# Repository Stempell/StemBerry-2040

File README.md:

# StemBerry-2040
A RP2040 devboard! Im doing it for Hack Club's Macondo program. It features two buttons for reset and bootsel and two onboard led's (one for power and one is hooked up to pin15), and also a cool evangelion-themed silkscreen art!
It plugs in to breadboards an female headers just like a standard pi pico.
I made this project to learn about making microcontrollers and more advanced pcb's and to have some microcontrollers for personal use. This project taught me a lot and it was also my first time working with restricted space on the board, so every trace and component placement had to be well thought.

The button on the left enters into BOOTSEL mode. The one on the right resets the board.
To upload code press the BOOTSEL button while booting up the board. It will then appear as a USB device on your pc, so you can drop the code in.

## Schematic

## Pcb

The dimensions are 21 x 51mm

## Full Bulid!

Here's the finished thing! :

## Bill of materials

| Component | Qty / board | Order qty | Ext. price | JLCPCB part |
|---|---|---|---|---|
| RP2040 | 1 | 5 | $4.94 | [C2040](https://jlcpcb.com/partdetail/C2040) |
| W25Q16JVUXIQ (flash) | 1 | 5 | $8.02 | [C2843335](https://jlcpcb.com/partdetail/C2843335) |
| XC6206P332MR-G (3.3V LDO) | 1 | 5 | $0.66 | [C5446](https://jlcpcb.com/partdetail/C5446) |
| 12MHz crystal | 1 | 5 | $0.47 | [C9002](https://jlcpcb.com/partdetail/C9002) |
| USB_C_Receptacle_USB2.0_14P | 1 | 5 | $0.92 | [C165948](https://jlcpcb.com/partdetail/C165948) |
| SW_Push | 2 | 10 | $0.55 | [C720477](https://jlcpcb.com/partdetail/C720477) |
| 100nF | 12 | 60 | $0.32 | [C1525](https://jlcpcb.com/partdetail/C1525) |
| 1uF | 2 | 10 | $0.16 | [C52923](https://jlcpcb.com/partdetail/C52923) |
| 10uF | 2 | 10 | $0.39 | [C19702](https://jlcpcb.com/partdetail/C19702) |
| 33pF | 2 | 10 | $0.07 | [C1562](https://jlcpcb.com/partdetail/C1562) |
| 5.1K | 2 | 10 | $0.06 | [C25905](https://jlcpcb.com/partdetail/C25905) |
| 27 | 2 | 20 | $0.03 | [C25156](https://jlcpcb.com/partdetail/C25156) |
| 1K | 2 | 10 | $0.07 | [C11702](https://jlcpcb.com/partdetail/C11702) |
| 10K | 1 | 5 | $0.04 | [C25744](https://jlcpcb.com/partdetail/C25744) |
| 330 | 1 | 5 | $0.04 | [C25104](https://jlcpcb.com/partdetail/C25104) |
| 470 | 1 | 5 | $0.03 | [C25117](https://jlcpcb.com/partdetail/C25117) |
| 100K | 1 | 5 | $0.04 | [C25741](https://jlcpcb.com/partdetail/C25741) |
| LED (0603) | 1 | 5 | $0.04 | [C2286](https://jlcpcb.com/partdetail/C2286) |
| LED (0805) | 1 | 5 | $0.08 | [C2297](https://jlcpcb.com/partdetail/C2297) |
| **Total** | | | **$16.93** | |

Additional charges and assembly costs rung me up $26.13
You will also need to hand solder two 1x20 male to male pin headers like these ones for like $3.17:

https://pl.aliexpress.com/item/1005007486600604.html?spm=a2g0o.detail.pcDetailTopMoreOtherSeller.1.3aacPweuPweunK&gps-id=pcDetailTopMoreOtherSeller&scm=1007.40050.354490.0&scm_id=1007.40050.354490.0&scm-url=1007.40050.354490.0&pvid=687313aa-89cb-461f-b6b6-9fdf85656003&_t=gps-id%3ApcDetailTopMoreOtherSeller%2Cscm-url%3A1007.40050.354490.0%2Cpvid%3A687313aa-89cb-461f-b6b6-9fdf85656003%2Ctpp_buckets%3A668%232846%238111%231996&pdp_ext_f=%7B%22order%22%3A%221255%22%2C%22eval%22%3A%221%22%2C%22sceneId%22%3A%2230050%22%2C%22fromPage%22%3A%22recommend%22%7D&pdp_npi=6%40dis%21PLN%214.29%214.29%21%21%211.12%211.12%21%400b88abba17864469134574151e101b%2112000040991067942%21rec%21PL%216850984236%21XZ%211%210%21n_tag%3A-29919%3Bd%3A9d0c4368%3Bm03_new_user%3A-29895&utparam-url=scene%3ApcDetailTopMoreOtherSeller%7Cquery_from%3A%7Cx_object_id%3A1005007486600604%7C_p_origin_prod%3A

Total cost: $44.43

If you wish to learn how to make a devboard like this one yourself, or any other devboard similar to this one check out the guide i used:

https://macondo.hackclub.com/docs/build-a-devboard

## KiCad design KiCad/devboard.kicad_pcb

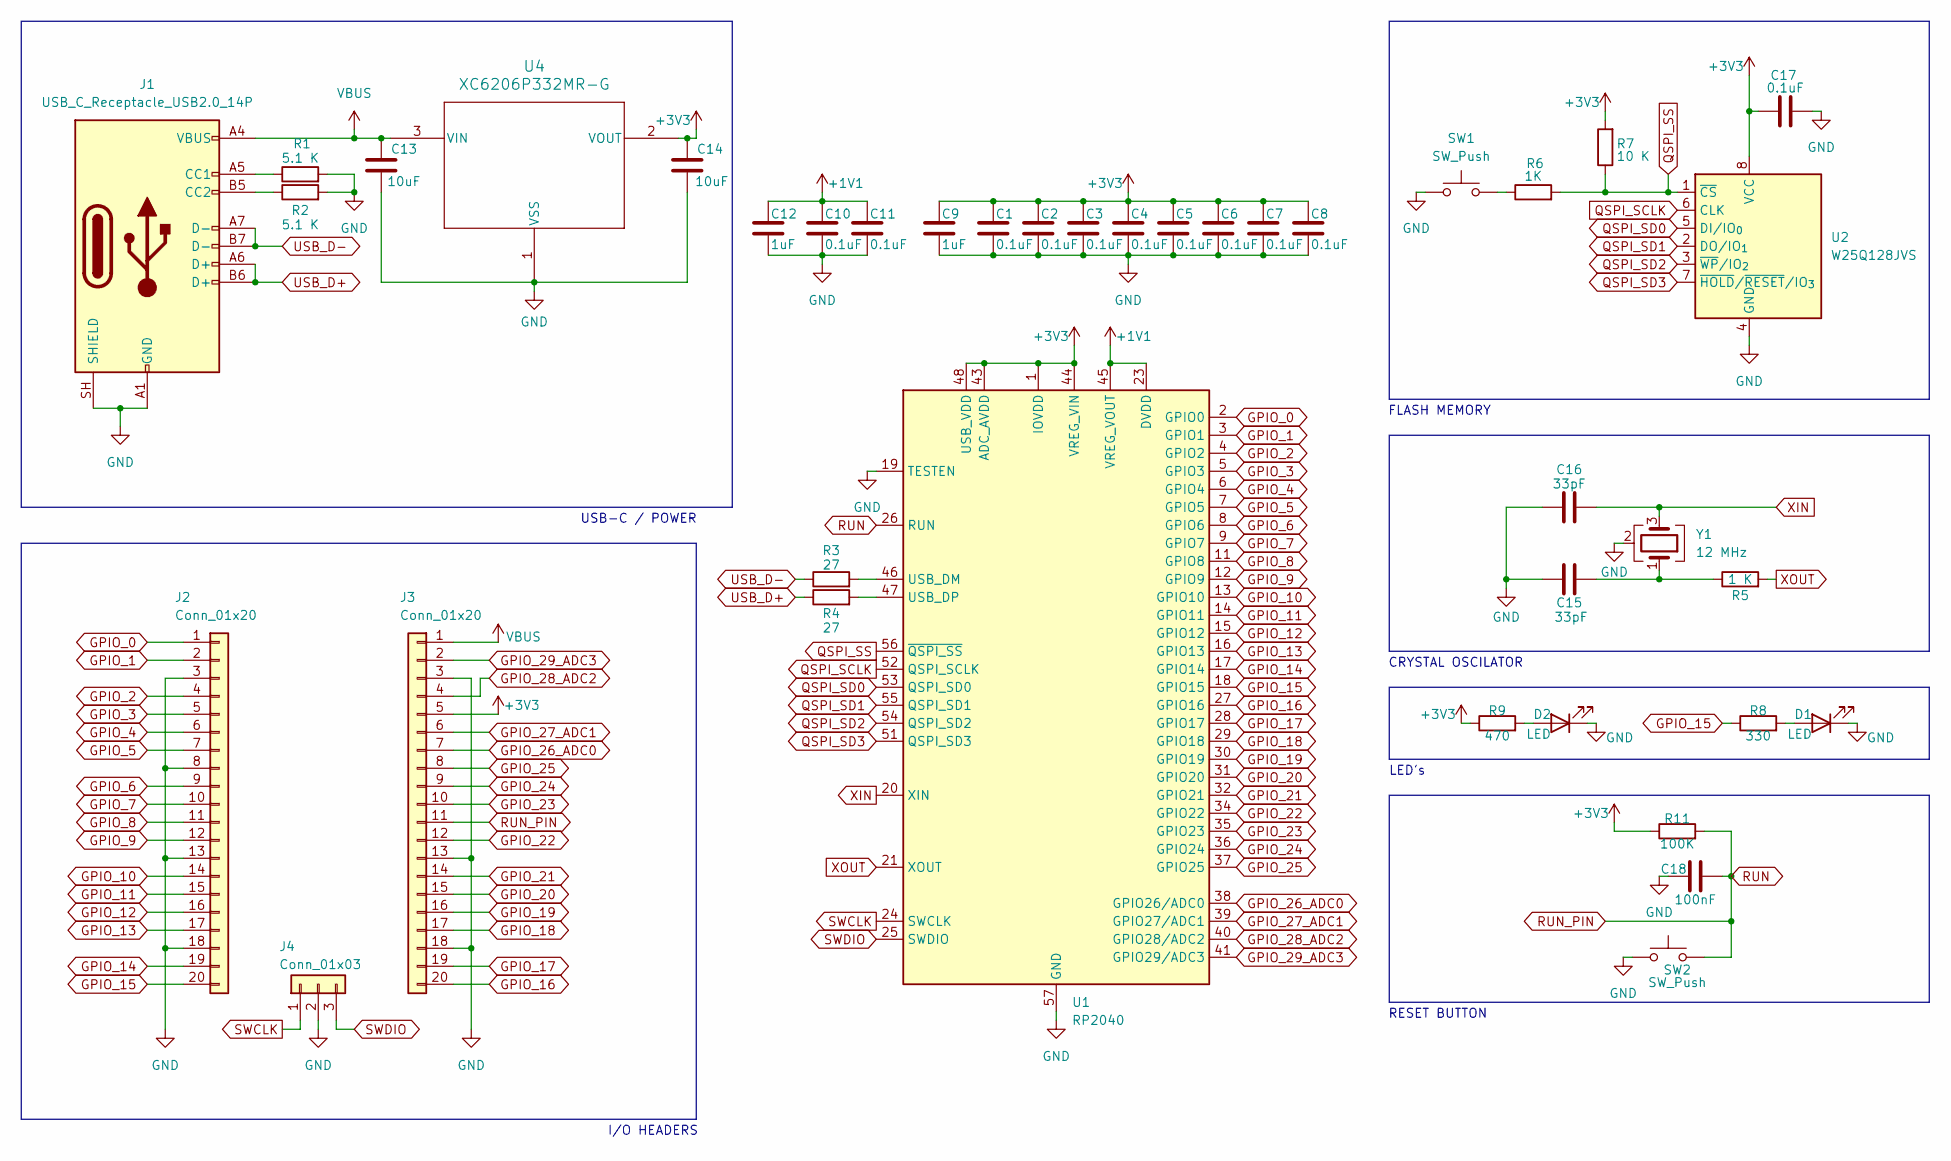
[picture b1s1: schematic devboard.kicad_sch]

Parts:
C1, C2, C3, C4, C5, C6, C7, C8, C10, C11, C17: 0.1uF; C_0402_1005Metric
C9, C12: 1uF; C_0402_1005Metric
C13, C14: 10uF; C_0603_1608Metric
C15, C16: 33pF; C_0402_1005Metric
C18: 100nF; C_0402_1005Metric
D1, D2: LED; LED_0603_1608Metric
J1: USB_C_Receptacle_USB2.0_14P; USB_C_Receptacle_HRO_TYPE-C-31-M-12
J2, J3: Conn_01x20; PinHeader_1x20_P2.54mm_Vertical
J4: Conn_01x03; PinHeader_1x03_P2.54mm_Vertical
R1, R2: 5.1 K; R_0402_1005Metric
R3, R4: 27; R_0402_1005Metric
R5: 1 K; R_0402_1005Metric
R6: 1K; R_0402_1005Metric
R7: 10 K; R_0402_1005Metric
R8: 330; R_0402_1005Metric
R9: 470; R_0402_1005Metric
R11: 100K; R_0402_1005Metric
SW1, SW2: SW_Push; SW_Push_SPST_NO_Alps_SKRK
U1: RP2040; QFN-56-1EP_7x7mm_P0.4mm_EP3.2x3.2mm
U2: W25Q128JVS; Winbond_USON-8-1EP_3x2mm_P0.5mm_EP0.2x1.6mm
U4: XC6206P332MR-G; SOT-23-3
Y1: 12 MHz; Crystal_SMD_3225-4Pin_3.2x2.5mm

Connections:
+1V1: C10.1, C11.1, C12.1, U1.23 (DVDD), U1.45 (VREG_VOUT), U1.50 (DVDD)
+3V3: C1.1, C2.1, C3.1, C4.1, C5.1, C6.1, C7.1, C8.1, C9.1, C14.1, C17.1, J3.5, R7.2, R9.1, R11.1, U1.1 (IOVDD), U1.10 (IOVDD), U1.22 (IOVDD), U1.33 (IOVDD), U1.42 (IOVDD), U1.43 (ADC_AVDD), U1.44 (VREG_VIN), U1.48 (USB_VDD), U1.49 (IOVDD), U2.8 (VCC), U4.2 (VOUT); also elsewhere on the board
GND: C1.2, C2.2, C3.2, C4.2, C5.2, C6.2, C7.2, C8.2, C9.2, C10.2, C11.2, C12.2, C13.2, C14.2, C15.1, C16.1, C17.2, C18.1, D1.1 (K), D2.1 (K), J1.A1 (GND), J1.A12 (GND), J1.B1 (GND), J1.B12 (GND), J1.SH (SHIELD), J2.3, J2.8, J2.13, J2.18, J3.3, J3.13, J3.18, J4.2, R1.2, R2.2, SW1.1, SW2.1, U1.19 (TESTEN), U1.57 (GND), U2.4 (GND), U4.1 (VSS), Y1.2 (G), Y1.4 (G); also elsewhere on the board
GPIO_0: J2.1, U1.2 (GPIO0)
GPIO_1: J2.2, U1.3 (GPIO1)
GPIO_2: J2.4, U1.4 (GPIO2)
GPIO_3: J2.5, U1.5 (GPIO3)
GPIO_4: J2.6, U1.6 (GPIO4)
GPIO_5: J2.7, U1.7 (GPIO5)
GPIO_6: J2.9, U1.8 (GPIO6)
GPIO_7: J2.10, U1.9 (GPIO7)
GPIO_8: J2.11, U1.11 (GPIO8)
GPIO_9: J2.12, U1.12 (GPIO9)
GPIO_10: J2.14, U1.13 (GPIO10)
GPIO_11: J2.15, U1.14 (GPIO11)
GPIO_12: J2.16, U1.15 (GPIO12)
GPIO_13: J2.17, U1.16 (GPIO13)
GPIO_14: J2.19, U1.17 (GPIO14)
GPIO_15: J2.20, R8.1, U1.18 (GPIO15)
GPIO_16: J3.20, U1.27 (GPIO16)
GPIO_17: J3.19, U1.28 (GPIO17)
GPIO_18: J3.17, U1.29 (GPIO18)
GPIO_19: J3.16, U1.30 (GPIO19)
GPIO_20: J3.15, U1.31 (GPIO20)
GPIO_21: J3.14, U1.32 (GPIO21)
GPIO_22: J3.12, U1.34 (GPIO22)
GPIO_23: J3.10, U1.35 (GPIO23)
GPIO_24: J3.9, U1.36 (GPIO24)
GPIO_25: J3.8, U1.37 (GPIO25)
GPIO_26_ADC0: J3.7, U1.38 (GPIO26/ADC0)
GPIO_27_ADC1: J3.6, U1.39 (GPIO27/ADC1)
GPIO_28_ADC2: J3.4, U1.40 (GPIO28/ADC2)
GPIO_29_ADC3: J3.2, U1.41 (GPIO29/ADC3)
unnamed: C15.2, R5.1, Y1.1
unnamed: D1.2 (A), R8.2
unnamed: D2.2 (A), R9.2
unnamed: J1.A5 (CC1), R1.1
unnamed: J1.B5 (CC2), R2.1
unnamed: R6.1, SW1.2
unnamed: R3.2, U1.46 (USB_DM)
unnamed: R4.2, U1.47 (USB_DP)
QSPI_SCLK: U1.52 (QSPI_SCLK), U2.6 (CLK)
QSPI_SD0: U1.53 (QSPI_SD0), U2.5 (DI/IO_{0})
QSPI_SD1: U1.55 (QSPI_SD1), U2.2 (DO/IO_{1})
QSPI_SD2: U1.54 (QSPI_SD2), U2.3 (~WP/IO_{2})
QSPI_SD3: U1.51 (QSPI_SD3), U2.7 (~HOLD/~RESET/IO_{3})
QSPI_SS: R6.2, R7.1, U1.56 (~QSPI_SS), U2.1 (~CS)
RUN: C18.2, J3.11, R11.2, SW2.2, U1.26 (RUN)
SWCLK: J4.1, U1.24 (SWCLK)
SWDIO: J4.3, U1.25 (SWDIO)
USB_D+: J1.A6 (D+), J1.B6 (D+), R4.1
USB_D-: J1.A7 (D-), J1.B7 (D-), R3.1
VBUS: C13.1, J1.A4 (VBUS), J1.A9 (VBUS), J1.B4 (VBUS), J1.B9 (VBUS), J3.1, U4.3 (VIN); also elsewhere on the board
XIN: C16.2, U1.20 (XIN), Y1.3
XOUT: R5.2, U1.21 (XOUT)

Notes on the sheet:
I/O HEADERS
USB-C / POWER
FLASH MEMORY
LED's
CRYSTAL OSCILATOR
RESET BUTTON

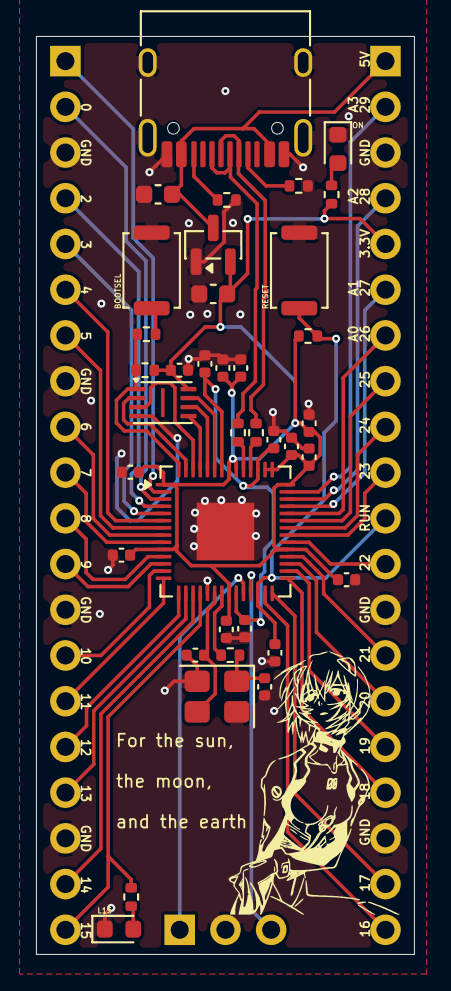
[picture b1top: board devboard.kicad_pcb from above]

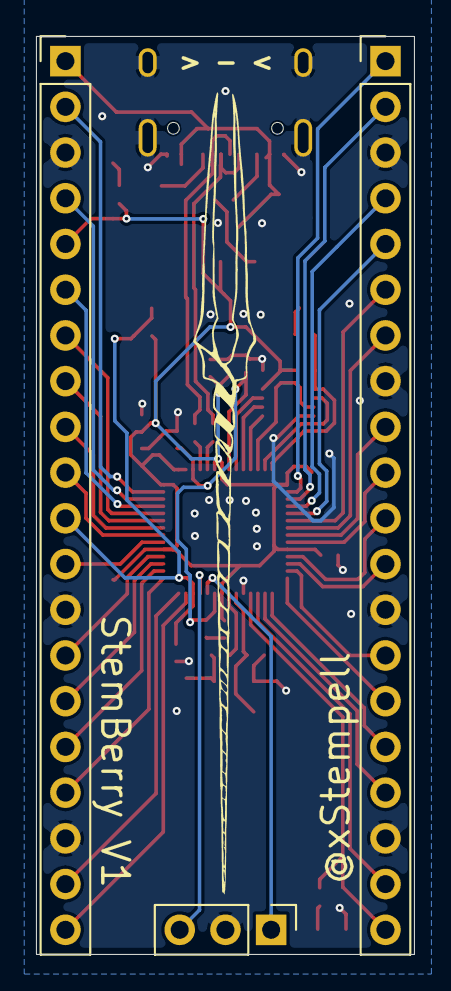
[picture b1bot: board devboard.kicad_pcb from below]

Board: 2 copper layers, 21.0 x 51.0 mm, 40 parts (3 on the bottom side), 55 nets.

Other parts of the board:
U3: MCP1700x-330xxTT; SOT-23

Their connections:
+3V3: U3.2 (VO); also elsewhere on the board
GND: U3.1 (GND); also elsewhere on the board
VBUS: U3.3 (VI); also elsewhere on the board

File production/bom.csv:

Designator,Footprint,Quantity,Value,LCSC Part #
"C1, C10, C11, C17, C2, C3, C4, C5, C6, C7, C8",0402,11,0.1uF,
"C12, C9",0402,2,1uF,
"C13, C14",0603,2,10uF,
"C15, C16",0402,2,33pF,
C18,0402,1,100nF,
"D1, D2",0603,2,LED,
J1,USB_C_Receptacle_HRO_TYPE-C-31-M-12,1,USB_C_Receptacle_USB2.0_14P,
"J2, J3",PinHeader_1x20_P2.54mm_Vertical,2,Conn_01x20,
J4,PinHeader_1x03_P2.54mm_Vertical,1,Conn_01x03,
"R1, R2",0402,2,5.1 K,
R11,0402,1,100K,
"R3, R4",0402,2,27,
R5,0402,1,1 K,
R6,0402,1,1K,
R7,0402,1,10 K,
R8,0402,1,330,
R9,0402,1,470,
"SW1, SW2",SW_Push_SPST_NO_Alps_SKRK,2,SW_Push,
U1,QFN-56-1EP_7x7mm_P0.4mm_EP3.2x3.2mm,1,RP2040,
U2,Winbond_USON-8-1EP_3x2mm_P0.5mm_EP0.2x1.6mm,1,W25Q128JVS,
U4,SOT-23-3,1,XC6206P332MR-G,
Y1,Crystal_SMD_3225-4Pin_3.2x2.5mm,1,12 MHz,
